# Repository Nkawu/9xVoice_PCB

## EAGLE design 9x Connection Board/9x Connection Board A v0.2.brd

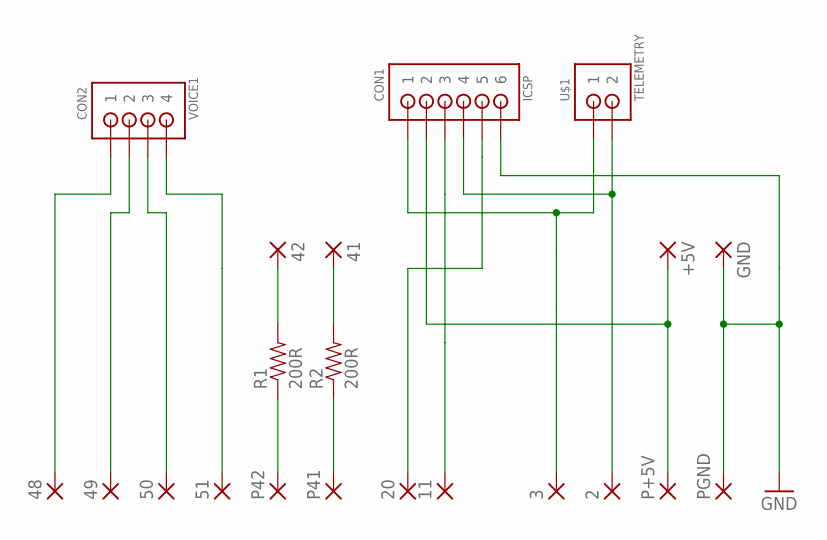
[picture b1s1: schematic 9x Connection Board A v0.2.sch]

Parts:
2, 3, 11, 20, 41, 42, 48, 49, 50, 51: WIREPADSMD1,27-254; SMD1,27-2,54
+5V: WIREPADSMD1,27-254; SMD1,27-2,54
CON1: ICSP; B6B-ZR
CON2: VOICE1; B4B-ZR
GND: WIREPADSMD1,27-254; SMD1,27-2,54
P41, P42: WIREPADSMD1,27-254; SMD1,27-2,54
P+5V: WIREPADSMD1,27-254; SMD1,27-2,54
PGND: WIREPADSMD1,27-254; SMD1,27-2,54
R1, R2: 200R; 0805
U$1: TELEMETRY; B2B-ZR

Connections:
+5V: +5V.1, CON1.2, P+5V.1
AD0: 51.1, CON2.4
AD1: 50.1, CON2.3
AD2: 49.1, CON2.2
AD3: 48.1, CON2.1
GND: CON1.6, GND.1, PGND.1
MISO: 3.1, CON1.1, U$1.1
MOSI: 2.1, CON1.4, U$1.2
unnamed: P42.1, R1.1
unnamed: P41.1, R2.1
unnamed: 42.1, R1.2
unnamed: 41.1, R2.2
RST: 20.1, CON1.5
SCK: 11.1, CON1.3

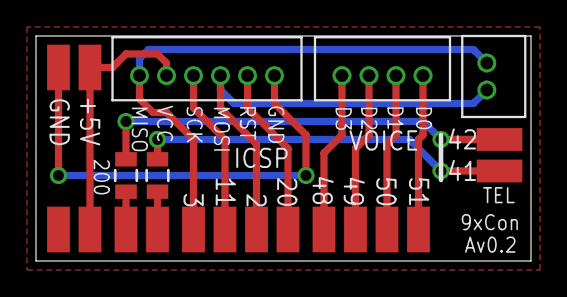
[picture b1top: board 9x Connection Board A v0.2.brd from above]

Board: 2 copper layers, 27.5 x 12.5 mm, 21 parts (0 on the bottom side), 14 nets.

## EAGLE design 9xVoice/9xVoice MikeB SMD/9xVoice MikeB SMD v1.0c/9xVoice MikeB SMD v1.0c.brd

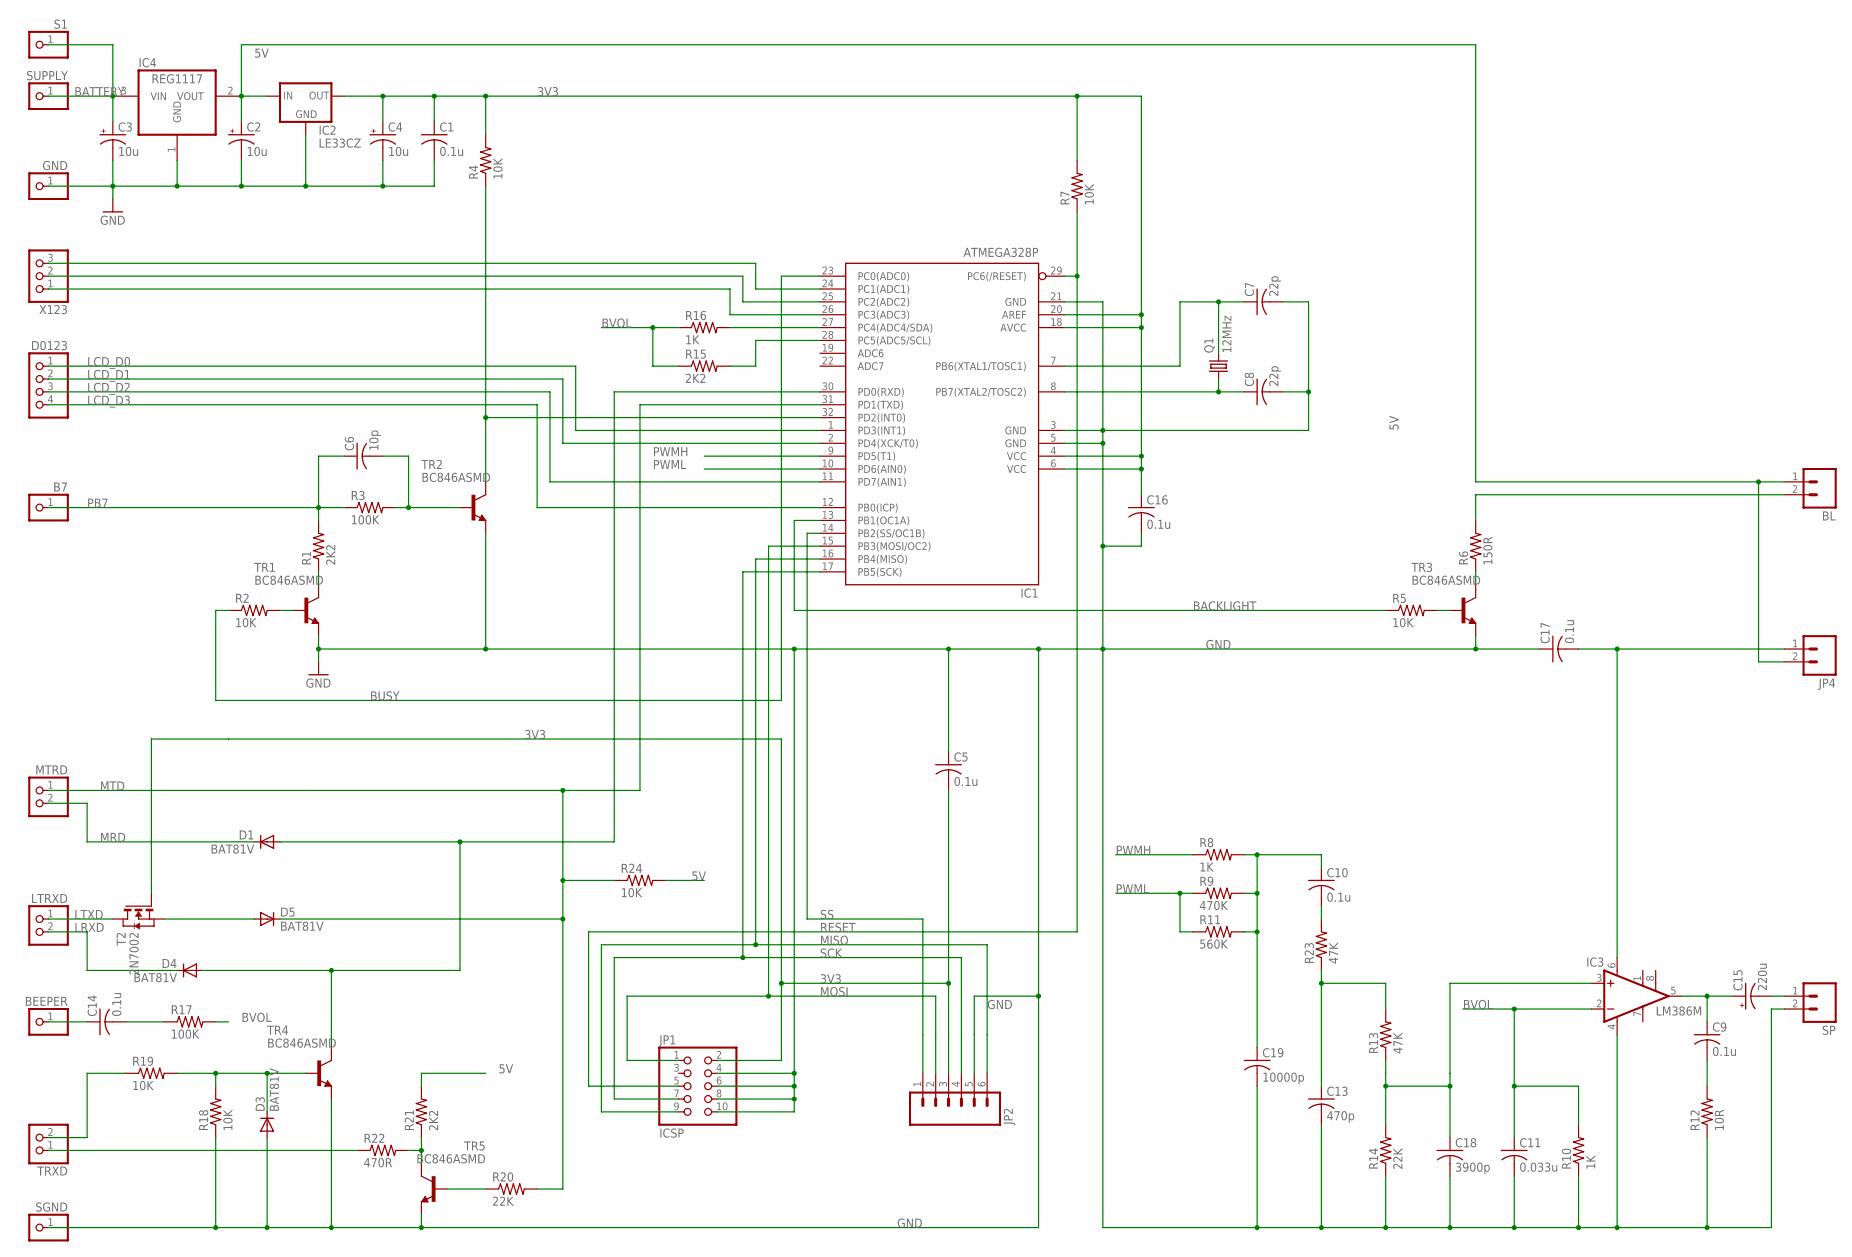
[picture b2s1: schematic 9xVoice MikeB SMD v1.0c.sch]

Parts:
B7: PINHD-1X1; 1X01
BEEPER: PINHD-1X1; 1X01
BL: M02PTH; 1X02
C1, C5, C9, C10, C14, C16, C17: 0.1u; C1206
C2, C3, C4: 10u; A/3216-18R
C6: 10p; C1206
C7, C8: 22p; C1206
C11: 0.033u; C1206
C13: 470p; C1206
C15: 220u; CT7343
C18: 3900p; C1206
C19: 10000p; C1206
D1, D3, D4, D5: BAT81V; SOD123
D0123: PINHD-1X4; 1X04
GND: PINHD-1X1; 1X01
IC1: ATMEGA328P; TQFP32-08; MPN ATMEGA8-16AU
IC2: LE33CZ; SOT23
IC3: LM386M; SO08
IC4: REG1117; SOT223
JP1: ICSP; 2X05
JP2: M06SIP; 1X06
JP4: M02PTH; 1X02
LTRXD: PINHD-1X2; 1X02
MTRD: PINHD-1X2; 1X02
Q1: 12MHz; 2-SMD
R1, R15, R21: 2K2; R1206
R2, R4, R5, R7, R18, R19, R24: 10K; R1206
R3, R17: 100K; R1206
R6: 150R; R1206
R8, R10, R16: 1K; R1206
R9: 470K; R1206
R11: 560K; R1206
R12: 10R; R1206
R13, R23: 47K; R1206
R14, R20: 22K; R1206
R22: 470R; R1206
S1: PINHD-1X1; 1X01
SGND: PINHD-1X1; 1X01
SP: M02PTH; 1X02
SUPPLY: PINHD-1X1; 1X01
T2: 2N7002; SOT-23
TR1, TR2, TR3, TR4, TR5: BC846ASMD; SOT23
TRXD: PINHD-1X2; 1X02
X123: PINHD-1X3; 1X03

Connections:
3V3: C1.1, C4.+, C5.2, C16.1, IC1.4 (VCC), IC1.6 (VCC), IC1.18 (AVCC), IC1.20 (AREF), IC2.2 (OUT), JP1.2, JP2.3, R4.2, R7.2, T2.3 (G)
5V: BL.1, C2.+, IC2.3 (IN), IC4.2 (VOUT), JP4.2, R21.2, R24.2
BACKLIGHT: IC1.13 (PB1(OC1A)), R5.1
BATTERY: C3.+, IC4.3 (VIN), S1.1, SUPPLY.1
BEEPER: BEEPER.1, C14.1
BUSY: IC1.23 (PC0(ADC0)), R2.1
BVOL: C11.1, IC3.2 (-IN), R10.2, R15.1, R16.1, R17.2
GND: C1.2, C2.-, C3.-, C4.-, C5.1, C7.2, C8.2, C11.2, C13.2, C16.2, C17.1, C18.2, C19.2, D3.A, GND.1, IC1.3 (GND), IC1.5 (GND), IC1.21 (GND), IC2.1 (GND), IC3.4 (GND), IC4.1 (GND), JP1.4, JP1.6, JP1.8, JP1.10, JP2.5, R10.1, R12.1, R14.1, R18.1, SGND.1, SP.2, TR1.2 (E), TR2.2 (E), TR3.2 (E), TR4.2 (E), TR5.2 (E)
LCD_D0: D0123.1, IC1.1 (PD3(INT1))
LCD_D1: D0123.2, IC1.2 (PD4(XCK/T0))
LCD_D2: D0123.3, IC1.11 (PD7(AIN1))
LCD_D3: D0123.4, IC1.12 (PB0(ICP))
LRXD: D4.C, LTRXD.2
LTXD: LTRXD.1, T2.1 (D)
MISO: IC1.16 (PB4(MISO)), JP1.9, JP2.6
MOSI: IC1.15 (PB3(MOSI/OC2)), JP1.1, JP2.2
MRD: D1.C, MTRD.2
MTD: D5.C, IC1.31 (PD1(TXD)), MTRD.1, R20.2, R24.1
unnamed: C13.1, R13.2, R23.1
unnamed: R21.1, R22.2, TR5.3 (C)
unnamed: R22.1, TRXD.1
unnamed: R20.1, TR5.1 (B)
unnamed: IC1.28 (PC5(ADC5/SCL)), R15.2
unnamed: IC1.27 (PC4(ADC4/SDA)), R16.2
unnamed: R19.1, TRXD.2
unnamed: D3.C, R18.2, R19.2, TR4.1 (B)
unnamed: D5.A, T2.2 (S)
unnamed: R1.1, TR1.3 (C)
unnamed: R2.2, TR1.1 (B)
unnamed: C6.2, R3.2, TR2.1 (B)
unnamed: C14.2, R17.1
unnamed: R5.2, TR3.1 (B)
unnamed: R6.1, TR3.3 (C)
unnamed: C10.2, R23.2
unnamed: IC1.32 (PD2(INT0)), R4.1, TR2.3 (C)
unnamed: C8.1, IC1.8 (PB7(XTAL2/TOSC2)), Q1.P$1 (1)
unnamed: C7.1, IC1.7 (PB6(XTAL1/TOSC1)), Q1.P$2 (2)
unnamed: BL.2, R6.2
unnamed: C9.1, C15.+, IC3.5 (OUT)
unnamed: C9.2, R12.2
unnamed: C15.-, SP.1
unnamed: C17.2, IC3.6 (VS), JP4.1
unnamed: C10.1, C19.1, R8.2, R9.2, R11.2
unnamed: C18.1, IC3.3 (+IN), R13.1, R14.2
PB7: B7.1, C6.1, R1.2, R3.1
PWMH: IC1.9 (PD5(T1)), R8.1
PWML: IC1.10 (PD6(AIN0)), R9.1, R11.1
RESET: IC1.29 (PC6(/RESET)), JP1.5, R7.1
RXD: D1.A, D4.A, IC1.30 (PD0(RXD)), TR4.3 (C)
SCK: IC1.17 (PB5(SCK)), JP1.7, JP2.4
SS: IC1.14 (PB2(SS/OC1B)), JP2.1
X1: IC1.26 (PC3(ADC3)), X123.1
X2: IC1.25 (PC2(ADC2)), X123.2
X3: IC1.24 (PC1(ADC1)), X123.3

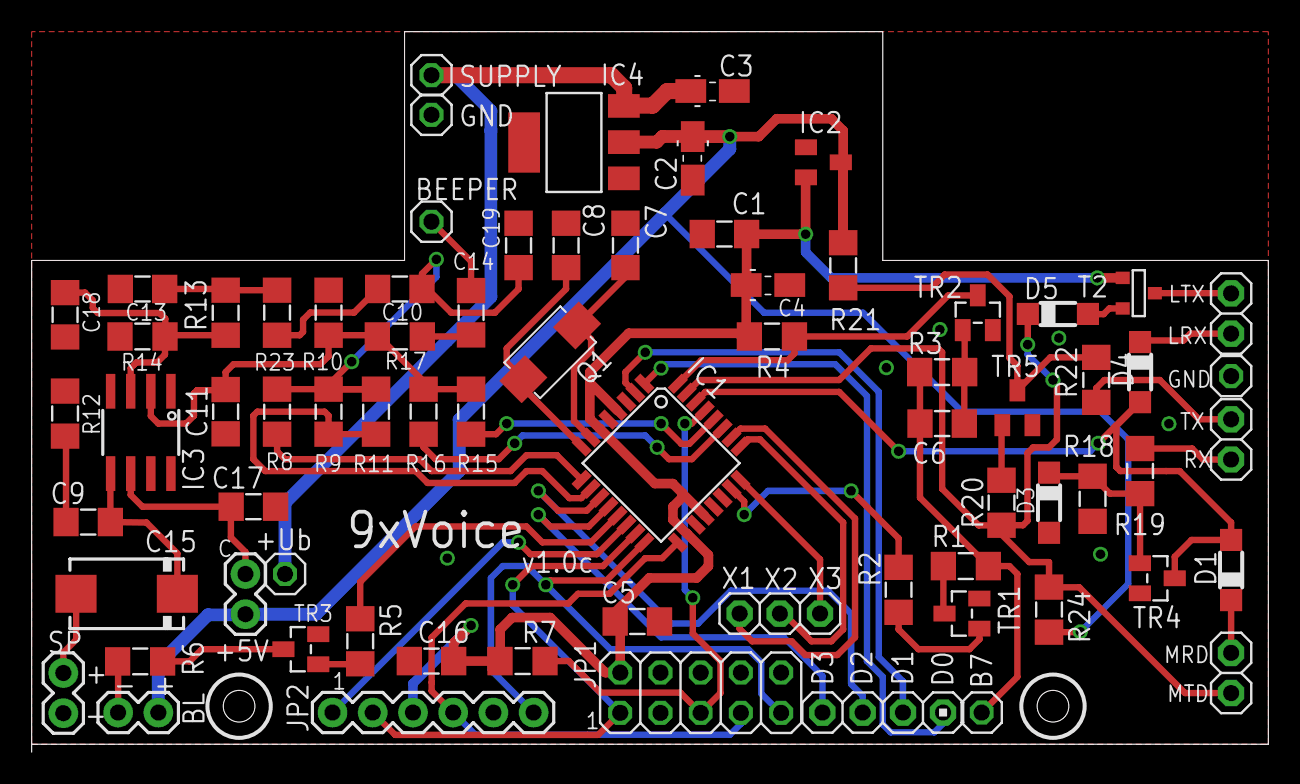
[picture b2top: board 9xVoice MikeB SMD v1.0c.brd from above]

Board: 2 copper layers, 78.1 x 45.0 mm, 73 parts (0 on the bottom side), 54 nets.

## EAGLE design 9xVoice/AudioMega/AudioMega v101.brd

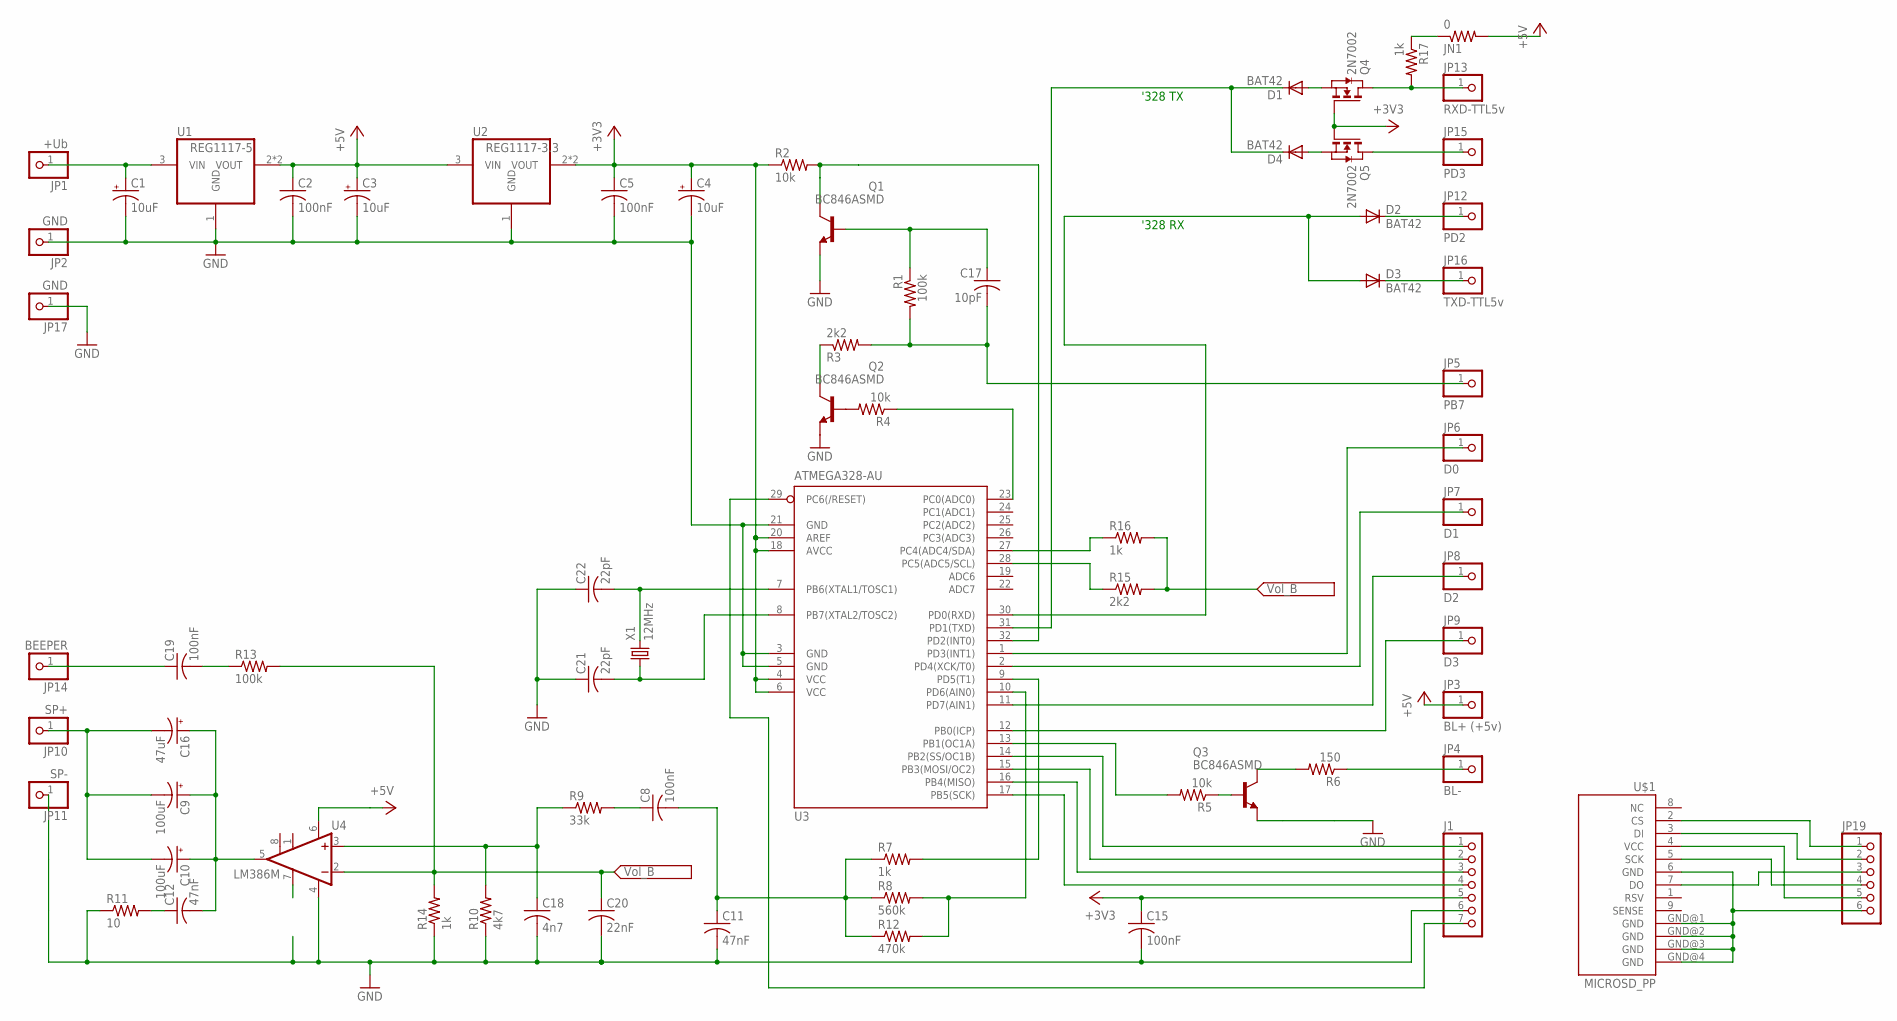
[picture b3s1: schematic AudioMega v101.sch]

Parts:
C1, C3, C4: 10uF; CT6032
C2, C5, C8, C15, C19: 100nF; C1206
C9, C10: 100uF; CT6032
C11, C12: 47nF; C1206
C16: 47uF; CT6032
C17: 10pF; C1206
C18: 4n7; C1206
C20: 22nF; C1206
C21, C22: 22pF; C1206
D1, D2, D3, D4: BAT42; SOD123
J1: PINHD-1X7; 1X07
JN1: 0; R1206
JP1: +Ub; 1X01
JP2, JP17: GND; 1X01
JP3: BL+ (+5v); 1X01
JP4: BL-; 1X01
JP5: PB7; 1X01
JP6: D0; 1X01
JP7: D1; 1X01
JP8: D2; 1X01
JP9: D3; 1X01
JP10: SP+; 1X01
JP11: SP-; 1X01
JP12: PD2; 1X01
JP13: RXD-TTL5v; 1X01
JP14: BEEPER; 1X01
JP15: PD3; 1X01
JP16: TXD-TTL5v; 1X01
JP19: PINHD-1X6; 1X06
Q1, Q2, Q3: BC846ASMD; SOT23
Q4, Q5: 2N7002; SOT-23
R1, R13: 100k; R1206
R2, R4, R5: 10k; R1206
R3, R15: 2k2; R1206
R6: 150; R1206
R7, R14, R16, R17: 1k; R1206
R8: 560k; R1206
R9: 33k; R1206
R10: 4k7; R1206
R11: 10; R1206
R12: 470k; R1206
U1: REG1117-5; SOT223
U2: REG1117-3.3; SOT223
U3: ATMEGA328-AU; TQFP32-08
U4: LM386M; SO08
U$1: MICROSD_PP
X1: 12MHz; HC49UP

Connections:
+3V3: C4.+, C5.1, C15.1, J1.5, Q4.3 (G), Q5.3 (G), R2.1, U2.2 (VOUT), U2.4 (VOUT), U3.4 (VCC), U3.6 (VCC), U3.18 (AVCC), U3.20 (AREF)
+5V: C2.1, C3.+, JN1.2, JP3.1, U1.2 (VOUT), U1.4 (VOUT), U2.3 (VIN), U4.6 (VS)
B7: C17.2, JP5.1, R1.2, R3.2
CLK: Q1.3 (C), R2.2, U3.32 (PD2(INT0))
GND: C1.-, C2.2, C3.-, C4.-, C5.2, C11.2, C15.2, C18.2, C20.2, C21.1, C22.1, J1.6, JP2.1, JP11.1, JP17.1, Q1.2 (E), Q2.2 (E), Q3.2 (E), R10.1, R11.1, R14.1, U1.1 (GND), U2.1 (GND), U3.3 (GND), U3.5 (GND), U3.21 (GND), U4.4 (GND)
unnamed: R4.1, U3.23 (PC0(ADC0))
unnamed: D4.A, Q5.2 (S)
unnamed: J1.2, U3.15 (PB3(MOSI/OC2))
unnamed: J1.3, U3.16 (PB4(MISO))
unnamed: J1.4, U3.17 (PB5(SCK))
unnamed: J1.7, U3.29 (PC6(/RESET))
unnamed: C22.2, U3.7 (PB6(XTAL1/TOSC1)), X1.2
unnamed: C21.2, U3.8 (PB7(XTAL2/TOSC2)), X1.1
unnamed: Q2.1 (B), R4.2
unnamed: R16.1, U3.27 (PC4(ADC4/SDA))
unnamed: R15.1, U3.28 (PC5(ADC5/SCL))
unnamed: Q2.3 (C), R3.1
unnamed: C17.1, Q1.1 (B), R1.1
unnamed: C9.-, C10.-, C16.-, JP10.1
unnamed: C12.1, R11.2
unnamed: C9.+, C10.+, C12.2, C16.+, U4.5 (OUT)
unnamed: C18.1, R9.1, R10.2, U4.3 (+IN)
unnamed: C19.1, JP14.1
unnamed: C19.2, R13.1
unnamed: J1.1, U3.14 (PB2(SS/OC1B))
unnamed: JN1.1, R17.1
unnamed: JP19.6, U$1.6 (GND), U$1.GND@1 (GND), U$1.GND@2 (GND), U$1.GND@3 (GND), U$1.GND@4 (GND)
unnamed: C8.1, R9.2
unnamed: C8.2, C11.1, R7.1, R8.1, R12.1
unnamed: Q3.3 (C), R6.2
unnamed: R7.2, U3.9 (PD5(T1))
unnamed: R8.2, R12.2, U3.10 (PD6(AIN0))
unnamed: JP4.1, R6.1
unnamed: JP9.1, U3.12 (PB0(ICP))
unnamed: JP8.1, U3.11 (PD7(AIN1))
unnamed: C1.+, JP1.1, U1.3 (VIN)
unnamed: Q3.1 (B), R5.1
unnamed: R5.2, U3.13 (PB1(OC1A))
unnamed: JP7.1, U3.2 (PD4(XCK/T0))
unnamed: JP6.1, U3.1 (PD3(INT1))
unnamed: D3.C, JP16.1
unnamed: JP15.1, Q5.1 (D)
unnamed: D2.C, JP12.1
unnamed: JP19.1, U$1.2 (CS)
unnamed: JP13.1, Q4.1 (D), R17.2
unnamed: D2.A, D3.A, U3.30 (PD0(RXD))
unnamed: JP19.2, U$1.3 (DI)
unnamed: JP19.3, U$1.7 (DO)
unnamed: D1.A, Q4.2 (S)
unnamed: D1.C, D4.C, U3.31 (PD1(TXD))
unnamed: JP19.4, U$1.5 (SCK)
unnamed: JP19.5, U$1.4 (VCC)
VOL_B: C20.1, R13.2, R14.2, R15.2, R16.2, U4.2 (-IN)

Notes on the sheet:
'328 RX
'328 TX

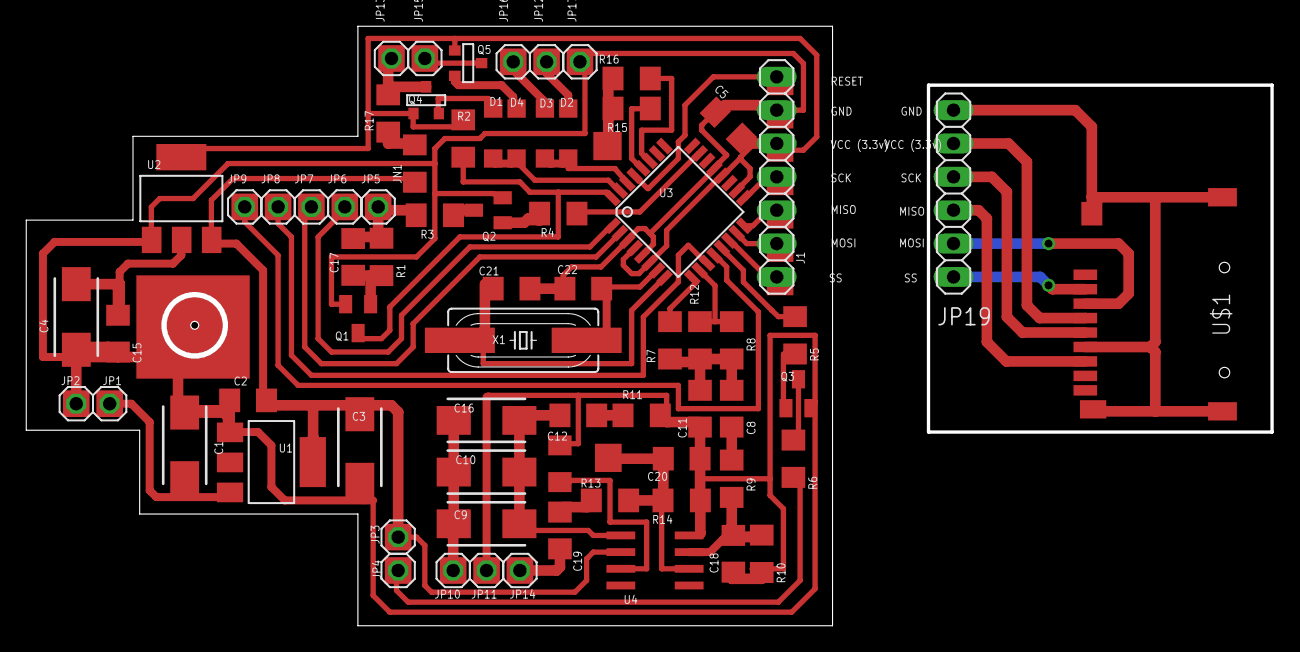
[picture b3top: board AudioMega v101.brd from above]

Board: 2 copper layers, 61.4 x 45.7 mm, 70 parts (0 on the bottom side), 53 nets.

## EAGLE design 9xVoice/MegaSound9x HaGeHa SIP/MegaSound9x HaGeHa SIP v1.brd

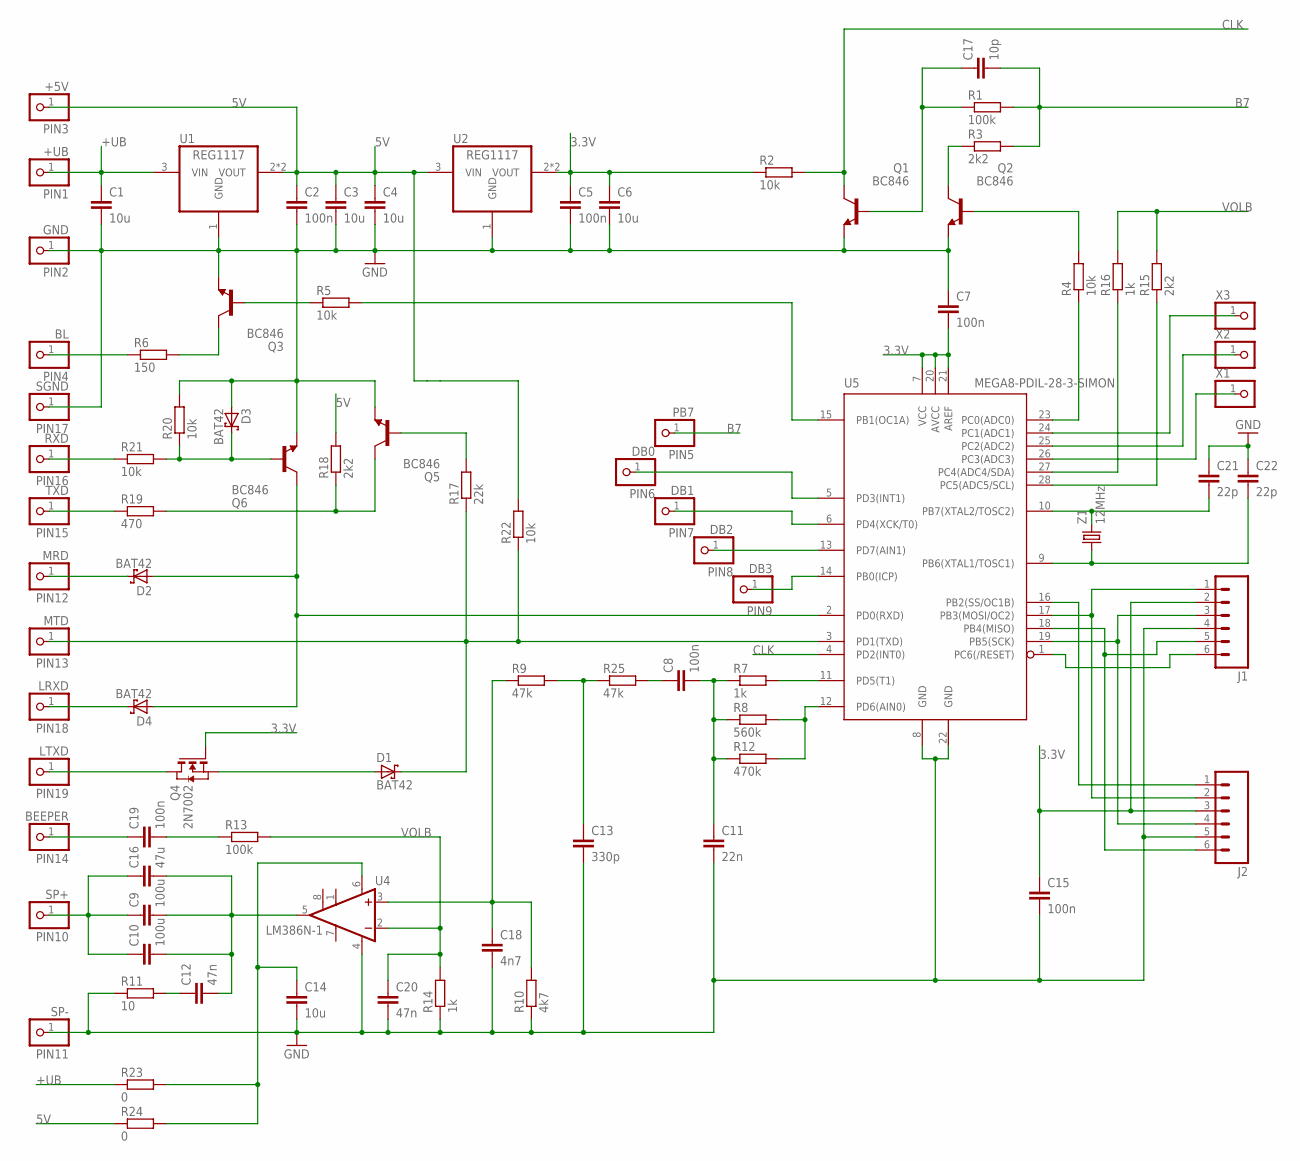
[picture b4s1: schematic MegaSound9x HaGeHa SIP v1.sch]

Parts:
+5V: PIN3; 1X01
+UB: PIN1; 1X01
BEEPER: PIN14; 1X01
BL: PIN4; 1X01
C1, C3, C4, C6, C14: 10u; C1206
C2, C5, C7, C8, C15, C19: 100n; C1206
C9, C10: 100u; C1206
C11: 22n; C1206
C12, C20: 47n; C1206
C13: 330p; C1206
C16: 47u; C1206
C17: 10p; C1206
C18: 4n7; C1206
C21, C22: 22p; C1206
D1, D2, D3, D4: BAT42; SOD123
DB0: PIN6; 1X01
DB1: PIN7; 1X01
DB2: PIN8; 1X01
DB3: PIN9; 1X01
GND: PIN2; 1X01
J1, J2: M06SIP; 1X06
LRXD: PIN18; 1X01
LTXD: PIN19; 1X01
MRD: PIN12; 1X01
MTD: PIN13; 1X01
PB7: PIN5; 1X01
Q1, Q2, Q3, Q5, Q6: BC846; SOT23
Q4: 2N7002; SOT-23
R1, R13: 100k; R1206
R2, R4, R5, R20, R21, R22: 10k; R1206
R3, R15, R18: 2k2; R1206
R6: 150; R1206
R7, R14, R16: 1k; R1206
R8: 560k; R1206
R9, R25: 47k; R1206
R10: 4k7; R1206
R11: 10; R1206
R12: 470k; R1206
R17: 22k; R1206
R19: 470; R1206
R23, R24: 0; R1206
RXD: PIN16; 1X01
SGND: PIN17; 1X01
SP+: PIN10; 1X01
SP-: PIN11; 1X01
TXD: PIN15; 1X01
U1: REG1117; SOT223
U2: REG1117; SOT223; MPN REG1117
U4: LM386N-1; DIL08
U5: MEGA8-PDIL-28-3-SIMON; DIL28-3-SIMON
X1, X2, X3: PINHD-1X1; 1X01
Z1: 12MHz; HC49US

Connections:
3.3V: C5.1, C6.1, C7.2, C15.1, J1.2, J2.3, Q4.3 (G), R2.1, U2.2 (VOUT), U2.4 (VOUT), U5.7 (VCC), U5.20 (AVCC), U5.21 (AREF)
5V: +5V.1, C2.1, C3.1, C4.1, R18.2, R22.2, R24.1, U1.2 (VOUT), U1.4 (VOUT), U2.3 (VIN)
+UB: +UB.1, C1.1, R23.1, U1.3 (VIN)
B7: C17.2, PB7.1, R1.2, R3.2
CLK: Q1.3 (C), R2.2, U5.4 (PD2(INT0))
D0: DB0.1, U5.5 (PD3(INT1))
GND: C1.2, C2.2, C3.2, C4.2, C5.2, C6.2, C7.1, C11.2, C13.2, C14.2, C15.2, C18.2, C20.2, C21.1, C22.1, D3.A, GND.1, J1.4, J2.5, Q1.2 (E), Q2.2 (E), Q3.2 (E), Q5.2 (E), Q6.2 (E), R10.1, R11.1, R14.1, R20.2, SGND.1, SP-.1, U1.1 (GND), U2.1 (GND), U4.4 (GND), U5.8 (GND), U5.22 (GND)
unnamed: C18.1, R9.1, R10.2, U4.3 (+IN)
unnamed: C12.1, R11.2
unnamed: C14.1, R23.2, R24.2, U4.6 (VS)
unnamed: C9.2, C10.2, C12.2, C16.2, U4.5 (OUT)
unnamed: C9.1, C10.1, C16.1, SP+.1
unnamed: BEEPER.1, C19.1
unnamed: C19.2, R13.1
unnamed: LTXD.1, Q4.1 (D)
unnamed: D1.A, Q4.2 (S)
unnamed: D4.C, LRXD.1
unnamed: D1.C, MTD.1, R17.1, R22.1, U5.3 (PD1(TXD))
unnamed: D2.C, MRD.1
unnamed: R19.1, TXD.1
unnamed: R21.1, RXD.1
unnamed: BL.1, R6.1
unnamed: Q5.3 (C), R18.1, R19.2
unnamed: Q3.3 (C), R6.2
unnamed: Q3.1 (B), R5.1
unnamed: Q2.1 (B), R4.2
unnamed: D3.C, Q6.1 (B), R20.1, R21.2
unnamed: Q5.1 (B), R17.2
unnamed: D2.A, D4.A, Q6.3 (C), U5.2 (PD0(RXD))
unnamed: R7.2, U5.11 (PD5(T1))
unnamed: C13.1, R9.2, R25.1
unnamed: C8.1, R25.2
unnamed: C8.2, C11.1, R7.1, R8.1, R12.1
unnamed: R8.2, R12.2, U5.12 (PD6(AIN0))
unnamed: DB3.1, U5.14 (PB0(ICP))
unnamed: DB2.1, U5.13 (PD7(AIN1))
unnamed: DB1.1, U5.6 (PD4(XCK/T0))
unnamed: Q2.3 (C), R3.1
unnamed: R5.2, U5.15 (PB1(OC1A))
unnamed: C17.1, Q1.1 (B), R1.1
unnamed: R4.1, U5.23 (PC0(ADC0))
unnamed: R16.1, U5.27 (PC4(ADC4/SDA))
unnamed: R15.1, U5.28 (PC5(ADC5/SCL))
unnamed: C21.2, U5.10 (PB7(XTAL2/TOSC2)), Z1.2
unnamed: C22.2, U5.9 (PB6(XTAL1/TOSC1)), Z1.1
unnamed: U5.24 (PC1(ADC1)), X3.1
unnamed: U5.25 (PC2(ADC2)), X2.1
unnamed: U5.26 (PC3(ADC3)), X1.1
unnamed: J1.3, J2.4, U5.19 (PB5(SCK))
unnamed: J1.5, J2.6, U5.18 (PB4(MISO))
unnamed: J1.6, U5.1 (PC6(/RESET))
unnamed: J1.1, J2.2, U5.17 (PB3(MOSI/OC2))
unnamed: J2.1, U5.16 (PB2(SS/OC1B))
VOLB: C20.1, R13.2, R14.2, R15.2, R16.2, U4.2 (-IN)

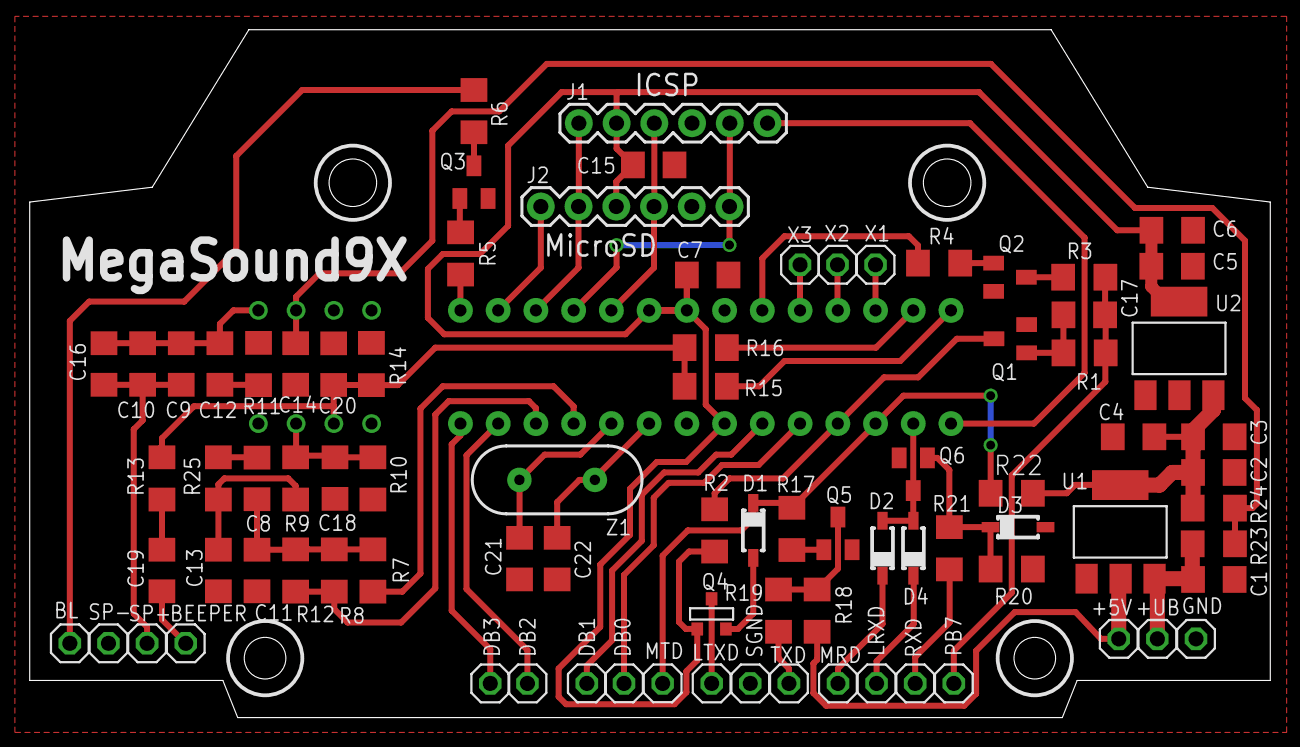
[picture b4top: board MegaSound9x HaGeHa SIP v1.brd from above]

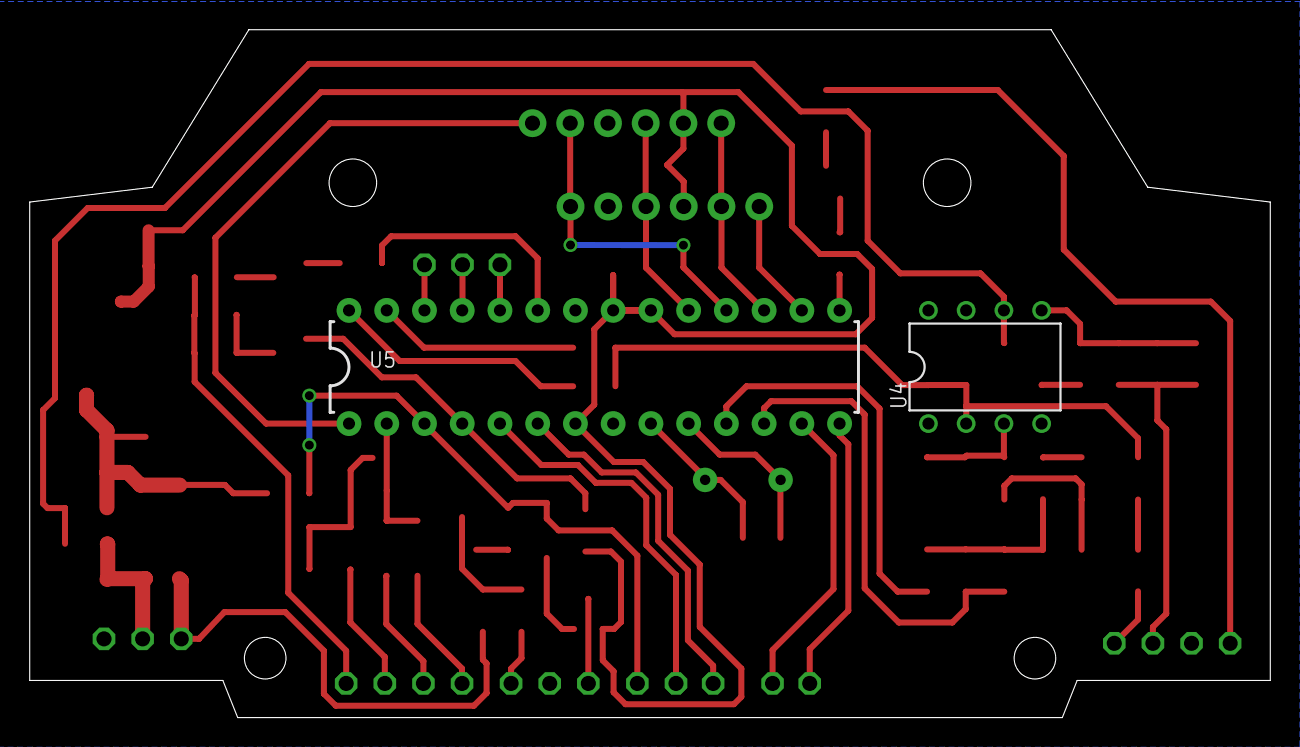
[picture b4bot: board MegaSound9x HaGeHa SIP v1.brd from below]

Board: 2 copper layers, 83.5 x 46.3 mm, 86 parts (2 on the bottom side), 54 nets.

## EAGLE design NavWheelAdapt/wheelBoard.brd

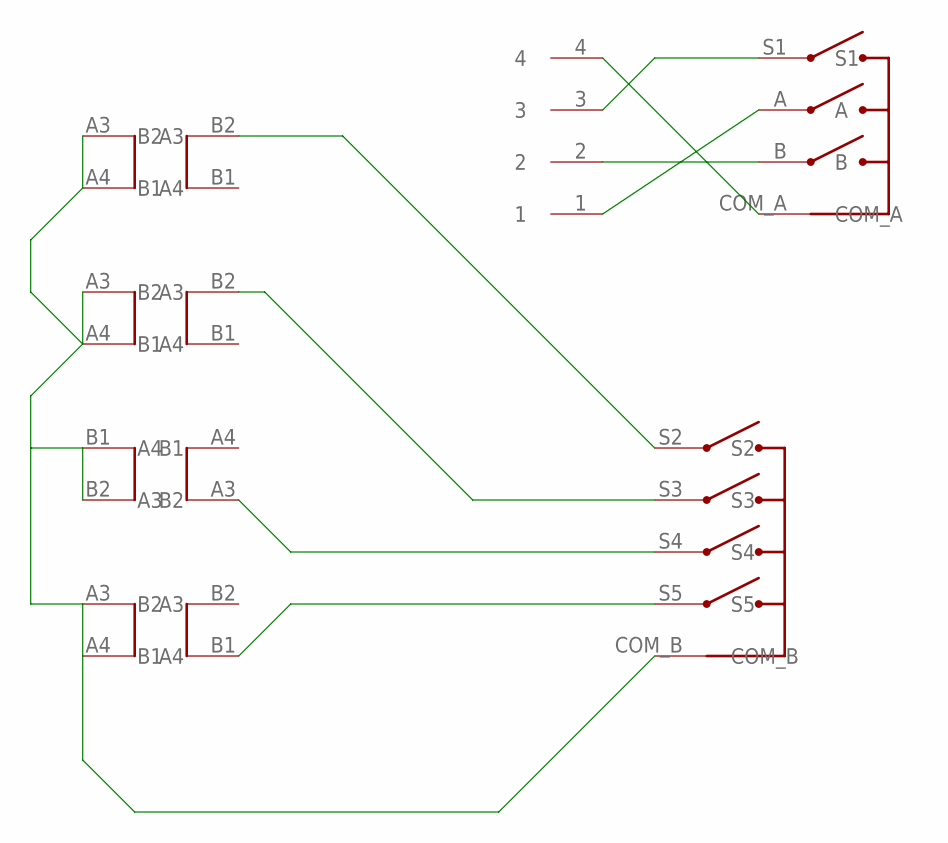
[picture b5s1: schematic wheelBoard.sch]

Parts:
U$1: TSWB-3N-CB222; W/DIREC
U$2, U$3, U$4, U$5: 9X_TACT_PATCH; 9XTACTPADS
U$6: 2MM_4P_HEADER; JST2MM_4P

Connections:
COM_A: U$1.COM_A, U$6.4
COM_B: U$1.COM_B, U$2.A3, U$2.A4, U$3.A3, U$3.A4, U$4.B1, U$4.B2, U$5.A3, U$5.A4
PHASE_A: U$1.A, U$6.1
PHASE_B: U$1.B, U$6.2
S2: U$1.S2, U$2.B2
S3: U$1.S3, U$3.B2
S4: U$1.S4, U$4.A3
S5: U$1.S5, U$5.B1
SELECT: U$1.S1, U$6.3

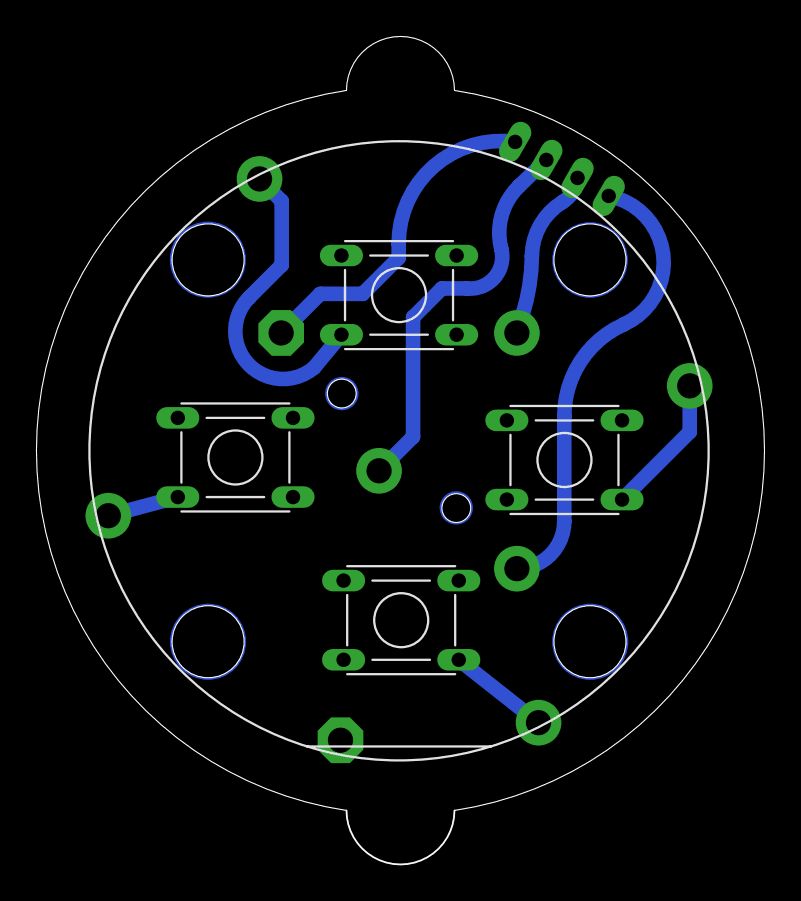
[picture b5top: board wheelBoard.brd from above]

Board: 2 copper layers, 40.4 x 46.0 mm, 6 parts (0 on the bottom side), 9 nets.

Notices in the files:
parts and their libraries:
SparkFun-Resistors: Licensing: CC v3.0 Share-Alike You are welcome to use this library for commercial purposes.
